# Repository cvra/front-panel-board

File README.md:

# Front Panel PCB

This small PCB is used to expose debug and HMI signals from inside the robot to
the external world through a front panel. The main goal is to simplify the
wiring and have a sturdy mount.

## Requirements

* USB Forwarding: Picoblade -> USB
* Ethernet forwarding: Picoblade -> RJ45
* CVRA debug forwarding
* CAN forwardig
* 6 LEDS + Team selection indication (RGB)
* 2 buttons for team selection
* Connector for the hall sensor starter: 5V, Signal, GND
* One connector to the nucleo shield for all GPIOs
* Max width: 80 mm, but lower is better
* Max length: 30mm
* Connectors must be at least 1.5mm off the board to go through the panel
* The board height should be as symmetrical as possible
* 2xM2 mounting holes.
* SWDIO exposed through something sturdier than Picoblade used in the past
* The silkscreen should document pinout to simplify troubleshooting

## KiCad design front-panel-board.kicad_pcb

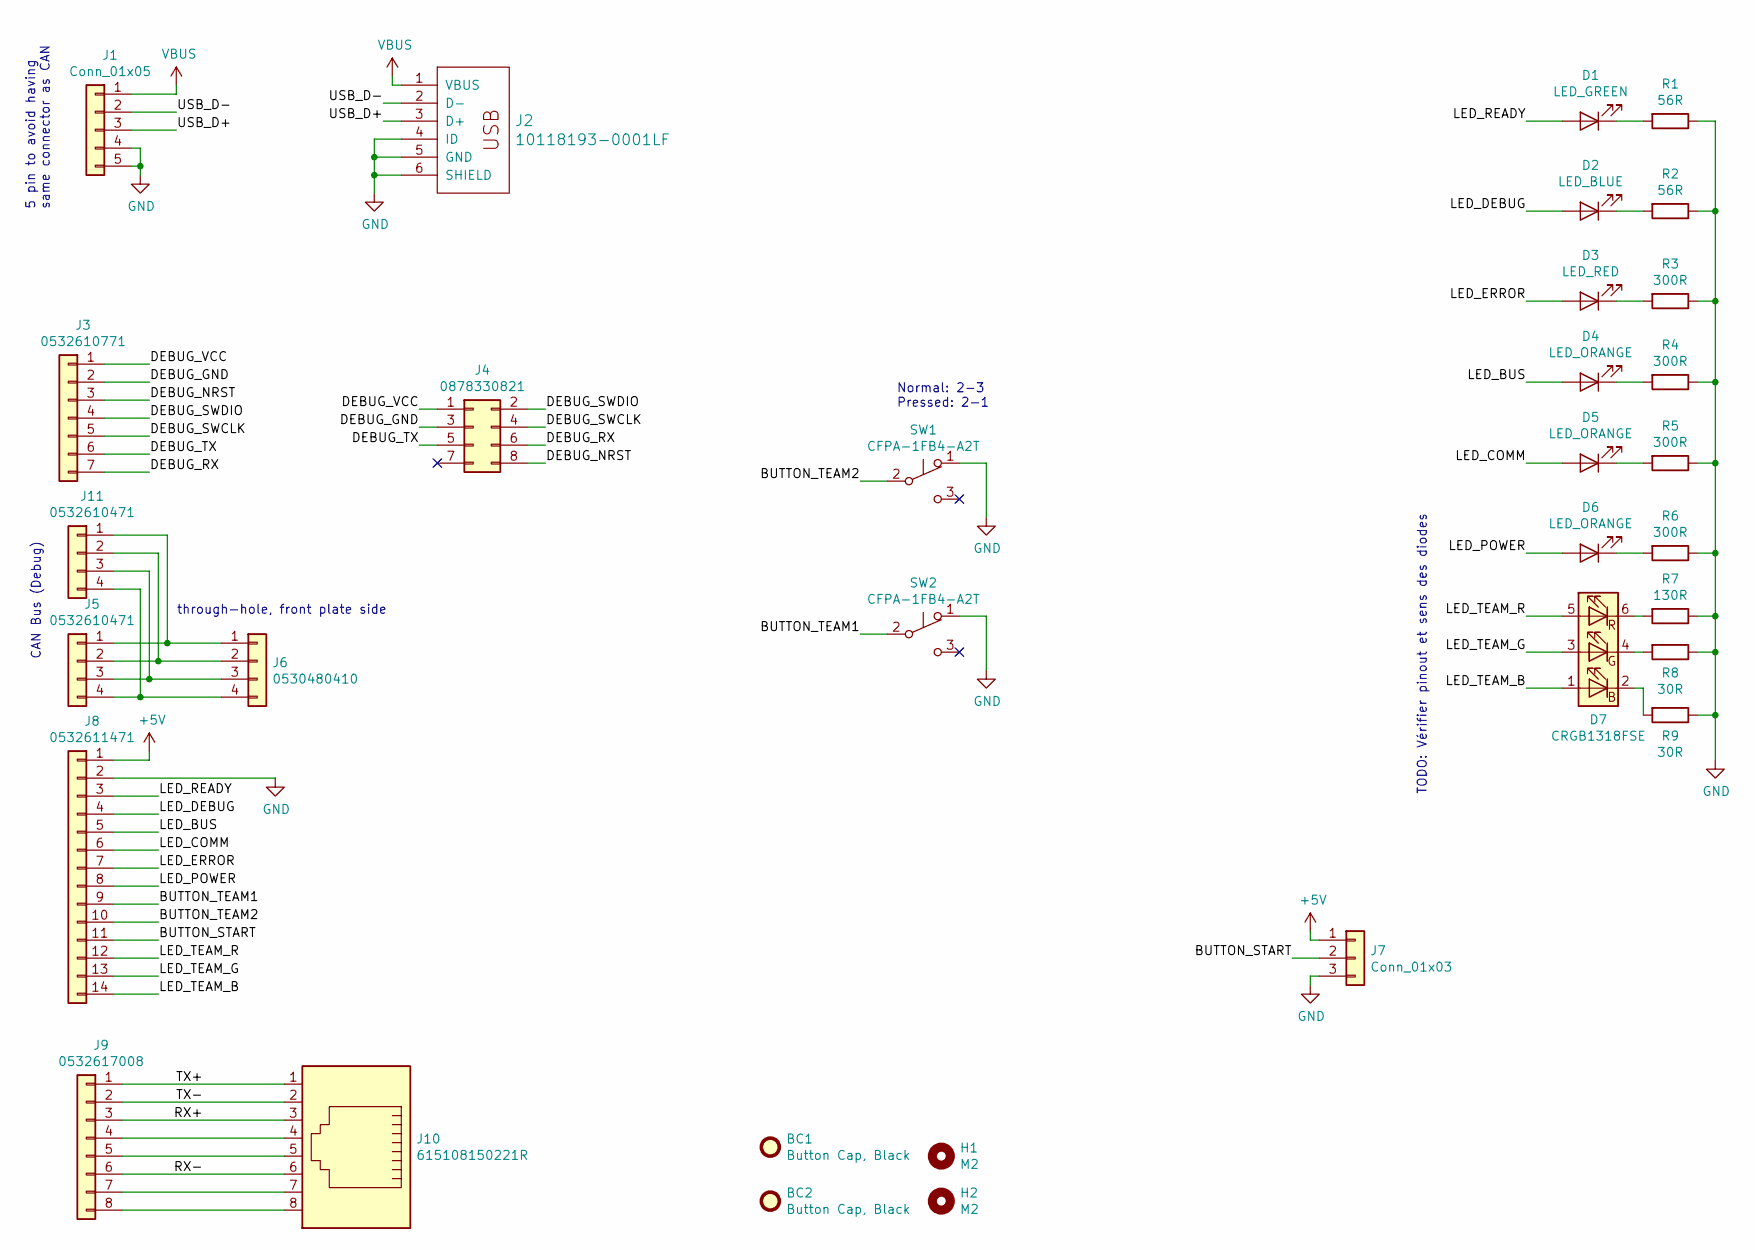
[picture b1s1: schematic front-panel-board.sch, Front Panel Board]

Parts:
BC1, BC2: Button Cap, Black; digikey# 563-1179-ND
D1: LED_GREEN; LED_0603_RightAngle; digikey# 160-1475-1-ND
D2: LED_BLUE; LED_0603_RightAngle; digikey# 1830-1029-1-ND
D3: LED_RED; LED_0603_RightAngle; digikey# 160-1479-1-ND
D4, D5, D6: LED_ORANGE; LED_0603_RightAngle; digikey# 160-1477-1-ND
D7: CRGB1318FSE; CRGB1318FSE-TM; digikey# 404-1264-1-ND
H1, H2: M2; MountingHole_2.2mm_M2_ISO14580
J1: Conn_01x05; Molex_PicoBlade_53261-0571_1x05-1MP_P1.25mm_Horizontal
J2: 10118193-0001LF; _Micro-USB-AB-receptacle-SMT-th-no-slot; digikey# 609-4616-1-ND
J3: 0532610771; Molex_PicoBlade_53261-0771_1x07-1MP_P1.25mm_Horizontal; digikey# WM7625CT-ND
J4: 0878330821; 0878330821_02x03_pin_header; digikey# WM23634-ND
J5, J11: 0532610471; Molex_PicoBlade_53261-0471_1x04-1MP_P1.25mm_Horizontal; digikey# WM7622TR-ND
J6: 0530480410; Molex-PicoBlade-4-Edge; digikey# WM1744-ND
J7: Conn_01x03; Molex_PicoBlade_53261-0371_1x03-1MP_P1.25mm_Horizontal
J8: 0532611471; Molex_PicoBlade_53261-1471_1x14-1MP_P1.25mm_Horizontal; digikey# WM7631CT-ND
J9: 0532617008; Molex_PicoBlade_53261-0871_1x08-1MP_P1.25mm_Horizontal; digikey# WM26501CT-ND
J10: 615108150221R; 615108150221R_Ethernet_MiddleMount; digikey# 732-13727-1-ND
R1, R2: 56R; R_0603_1608Metric_Pad1.05x0.95mm_HandSolder
R3, R4, R5, R6: 300R; R_0603_1608Metric_Pad1.05x0.95mm_HandSolder
R7: 130R; R_0603_1608Metric_Pad1.05x0.95mm_HandSolder
R8, R9: 30R; R_0603_1608Metric_Pad1.05x0.95mm_HandSolder
SW1, SW2: CFPA-1FB4-A2T; digikey# 563-1246-1-ND

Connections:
+5V: J7.1, J8.1
/BUTTON_START: J7.2, J8.11
/BUTTON_TEAM1: J8.9, SW2.2 (B)
/BUTTON_TEAM2: J8.10, SW1.2 (B)
/DEBUG_GND: J3.2, J4.3
/DEBUG_NRST: J3.3, J4.8
/DEBUG_RX: J3.7, J4.6
/DEBUG_SWCLK: J3.5, J4.4
/DEBUG_SWDIO: J3.4, J4.2
/DEBUG_TX: J3.6, J4.5
/DEBUG_VCC: J3.1, J4.1
/LED_BUS: D4.2 (A), J8.5
/LED_COMM: D5.2 (A), J8.6
/LED_DEBUG: D2.2 (A), J8.4
/LED_ERROR: D3.2 (A), J8.7
/LED_POWER: D6.2 (A), J8.8
/LED_READY: D1.2 (A), J8.3
/LED_TEAM_B: D7.1 (BA), J8.14
/LED_TEAM_G: D7.3 (GA), J8.13
/LED_TEAM_R: D7.5 (RA), J8.12
/RX+: J9.3, J10.3
/RX-: J9.6, J10.6
/TX+: J9.1, J10.1
/TX-: J9.2, J10.2
/USB_D+: J1.3, J2.3 (D+)
/USB_D-: J1.2, J2.2 (D-)
GND: J1.4, J1.5, J2.4 (ID), J2.5 (GND), J2.6 (SHIELD), J7.3, J8.2, R1.1, R2.1, R3.1, R4.1, R5.1, R6.1, R7.1, R8.1, R9.1, SW1.1 (A), SW2.1 (A)
unnamed: D1.1 (K), R1.2
unnamed: D2.1 (K), R2.2
unnamed: D3.1 (K), R3.2
unnamed: D4.1 (K), R4.2
unnamed: D5.1 (K), R5.2
unnamed: D6.1 (K), R6.2
unnamed: D7.2 (BK), R9.2
unnamed: D7.4 (GK), R8.2
unnamed: D7.6 (RK), R7.2
unnamed: J9.4, J10.4
unnamed: J9.5, J10.5
unnamed: J9.7, J10.7
unnamed: J9.8, J10.8
unnamed: J5.1, J6.1, J11.1
unnamed: J5.2, J6.2, J11.2
unnamed: J5.3, J6.3, J11.3
unnamed: J5.4, J6.4, J11.4
VBUS: J1.1, J2.1 (VBUS)

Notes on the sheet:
Normal: 2-3 Pressed: 2-1
through-hole, front plate side
TODO: Vérifier pinout et sens des diodes
CAN Bus (Debug)
5 pin to avoid having same connector as CAN

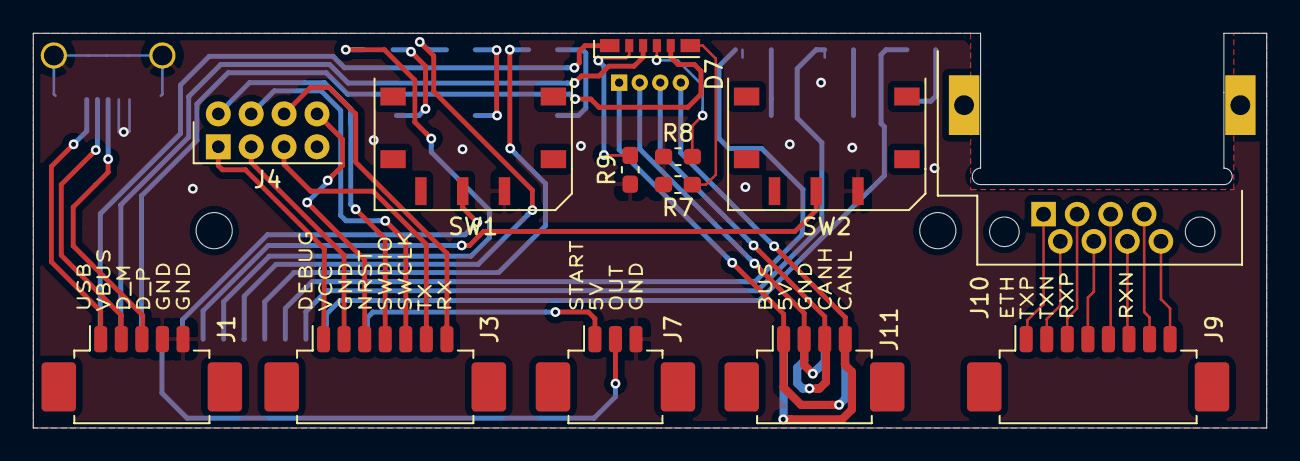
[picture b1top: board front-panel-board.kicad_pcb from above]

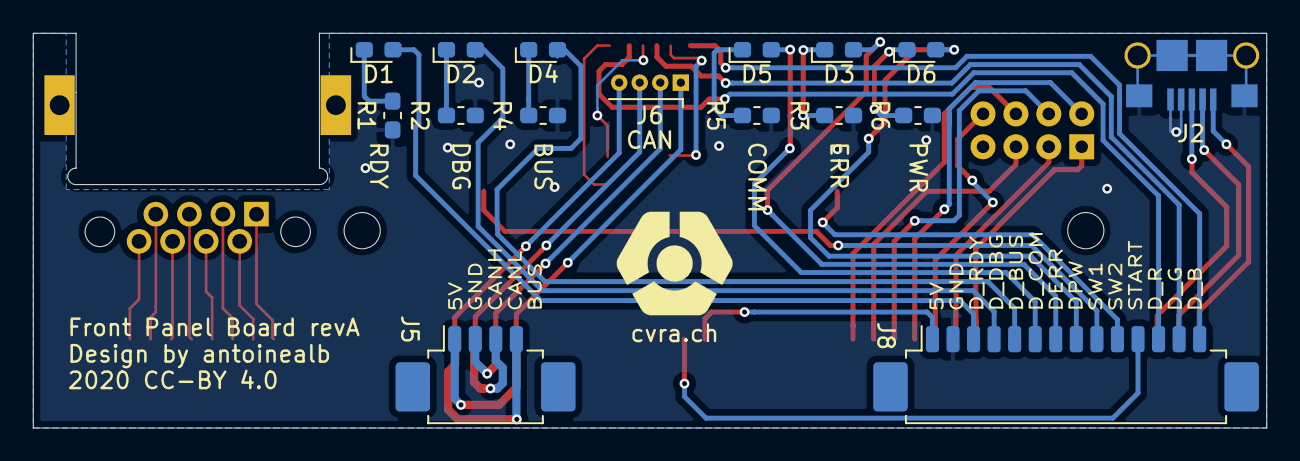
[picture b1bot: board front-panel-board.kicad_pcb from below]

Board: 2 copper layers, 75.0 x 24.0 mm, 31 parts (16 on the bottom side), 45 nets.

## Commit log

2020-03-15 root
2020-03-15 gitignore
2020-03-15 Empty project
2020-03-15 Add cvra kicad lib
2020-03-19 add readme with requirements
2020-03-19 Basic schematic
2020-03-19 Update kicad-lib
2020-04-10 Add chosen components datasheets
2020-04-10 First revision of the front panel board
2020-04-10 Cleanup a bit the README
2020-04-10 Add a license
2020-04-17 Fixes after PCB review
    * Bump trace width to 0.3 mm everywhere (except RJ45 conn)
    * Bump clearance to 0.2 mm everywhere (except RJ45 conn)
    * Reduced thermal relief width
    * Improved ground plane
    * Cleaned up USB connector routing / silkscreen
    * Moved mechanical elements after review by mechanical engineering.
2020-04-17 Add board dimensions to README
2020-04-17 Use red LEDs instead of orange ones, as they are OoS
2020-04-17 Add notes on female programming cable manufacturing
2020-04-18 Minor fixes
    * Add a CVRA logo in copper
    * Move around some tracks
    * Make more tracks 0.3mm

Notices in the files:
front-panel-board.kicad_pcb:
2020 CC-BY 4.0
front-panel-board.sch:
CC-BY 4.0
